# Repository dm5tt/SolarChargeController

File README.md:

# Description

A small TI BQ24074 solar charger inspired by the Adafruit design with some modifications:

 - Protection diode replaced with a PMOS to get rid of the diode voltage drop
 - Added a M3406-ADJ to get clean 3.3V
 - Big Cs to catch transients
 - Filter to get rid of most of the ripple caused by the buck

# Important

Thermistor TH1 must *always* be soldered. 

If you don't want to use one: solder a 10k 0805 resistor.

# Configuration

| **OUT Voltage** | **R10** | **R11** |
|---------|-------------|---------|
| 1.8V    |  Todo       | Todo    |
| 3.3V    |  Todo       | Todo    |

| **Charging current max.**   | **EN1** | **EN2** |
|-------------|----------|---------|
|  500mA |   Dot    |  No Dot |
|  100mA |   No Dot |  No Dot |

# Most important datasheets

[TI BQ24074](https://www.ti.com/lit/gpn/bq24074)

[XI'AN Aerosemi Tech M3406-ADJ](https://www.lcsc.com/datasheet/lcsc_datasheet_2304140030_XI-AN-Aerosemi-Tech-M3406-ADJ_C83224.pdf)

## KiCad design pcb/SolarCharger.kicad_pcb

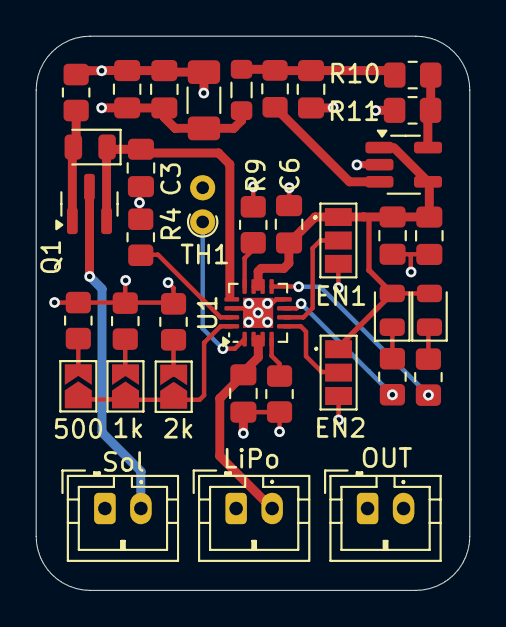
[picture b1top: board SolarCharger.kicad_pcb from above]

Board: 4 copper layers, 24.1 x 30.8 mm, 37 parts (0 on the bottom side), 24 nets.

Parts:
C1: 4.7uF; C_0805_2012Metric_Pad1.18x1.45mm_HandSolder
C2, C6, C7: 1uF; C_0805_2012Metric_Pad1.18x1.45mm_HandSolder
C3: 42uF; C_0805_2012Metric_Pad1.18x1.45mm_HandSolder
C4: 10uF; C_0805_2012Metric_Pad1.18x1.45mm_HandSolder
C5, C8: 0.1uF; C_0805_2012Metric_Pad1.18x1.45mm_HandSolder
C9: 100uF; C_1206_3216Metric_Pad1.33x1.80mm_HandSolder
D1, D2: LED; LED_0805_2012Metric
D3: D_Schottky; D_0805_2012Metric
FB2: FerriteBead_Small; L_0805_2012Metric_Pad1.05x1.20mm_HandSolder
J1, J2, J3: Conn_01x02_Pin; JST_PH_B2B-PH-K_1x02_P2.00mm_Vertical
JP1, JP2, JP3: SolderJumper_2_Open; SolderJumper-2_P1.3mm_Open_TrianglePad1.0x1.5mm
JP4, JP5: SolderJumper_3_Open; SolderJumper-3_P1.3mm_Open_Pad1.0x1.5mm_NumberLabels
L1: 2.2uH; L_0805_2012Metric_Pad1.15x1.40mm_HandSolder
Q1: AO3401A; SOT-23
R1: 590; R_0805_2012Metric_Pad1.20x1.40mm_HandSolder
R2, R9: 1k; R_0805_2012Metric_Pad1.20x1.40mm_HandSolder
R3: 2k; R_0805_2012Metric_Pad1.20x1.40mm_HandSolder
R4, R5, R6, R7: 10k; R_0805_2012Metric_Pad1.20x1.40mm_HandSolder
R8: 100k; R_0805_2012Metric_Pad1.20x1.40mm_HandSolder
R10, R11: R; R_0805_2012Metric_Pad1.20x1.40mm_HandSolder
TH1: Thermistor; R_Axial_DIN0204_L3.6mm_D1.6mm_P1.90mm_Vertical
U1: BQ24074; VQFN-16-1EP_3x3mm_P0.5mm_EP1.68x1.68mm
U2: M3406-ADJ; SOT-23-5_HandSoldering

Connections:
+3.3V: C7.1, C8.1, C9.1, FB2.2, J3.2
/OUT: C1.1, C5.1, C6.2, D1.2 (A), D2.2 (A), JP4.3 (B), JP5.3 (B), U1.10 (OUT), U1.11 (OUT), U2.1 (RUN), U2.4 (VIN)
/VBUS: C3.1, D3.1 (K), Q1.2 (S), U1.13 (IN)
/VLIPO: C2.2, J1.2, U1.2 (BAT), U1.3 (BAT)
GND: C1.2, C2.1, C3.2, C4.2, C5.2, C6.1, C7.2, C8.2, C9.2, J1.1, J2.1, J3.1, JP4.1 (A), JP5.1 (A), R1.1, R2.1, R3.1, R4.2, R5.2, R8.1, R9.1, R11.2, TH1.2, U1.8 (Vss), U1.14 (TMR), U1.17 (Vss), U2.2 (GND)
unnamed: C4.1, FB2.1, L1.2, R10.1
unnamed: D1.1 (K), R7.2
unnamed: D2.1 (K), R6.2
unnamed: D3.2 (A), Q1.1 (G), R8.2
unnamed: J2.2, Q1.3 (D)
unnamed: JP1.1 (A), JP2.1 (A), JP3.1 (A), U1.16 (ISET)
unnamed: JP1.2 (B), R1.2
unnamed: JP2.2 (B), R2.2
unnamed: JP3.2 (B), R3.2
unnamed: JP4.2 (C), U1.6 (EN1)
unnamed: JP5.2 (C), U1.5 (EN2)
unnamed: R5.1, U1.4 (CE)
unnamed: R6.1, U1.9 (CHG)
unnamed: R9.2, U1.12 (ILIM)
unnamed: R4.1, U1.15 (ITERM)
unnamed: R7.1, U1.7 (PGOOD)
unnamed: TH1.1, U1.1 (TS)
unnamed: R10.2, R11.1, U2.5 (FB)
unnamed: L1.1, U2.3 (SW)

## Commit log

2024-04-17 pcb: smaller eyecandy stuff. No functional changes.
2024-04-17 doc: replace with with new pcb
2024-04-17 pcb: eyecandy stuff destoryed the solderbridge marker
2024-05-26 pcb, schematic: get rid of non-standard p-mosfet and replace it with an AO3401
